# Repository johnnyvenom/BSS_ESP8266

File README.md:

# BSS_ESP8266
ESP8266 scripts and patches for Body:Suit:Score tests

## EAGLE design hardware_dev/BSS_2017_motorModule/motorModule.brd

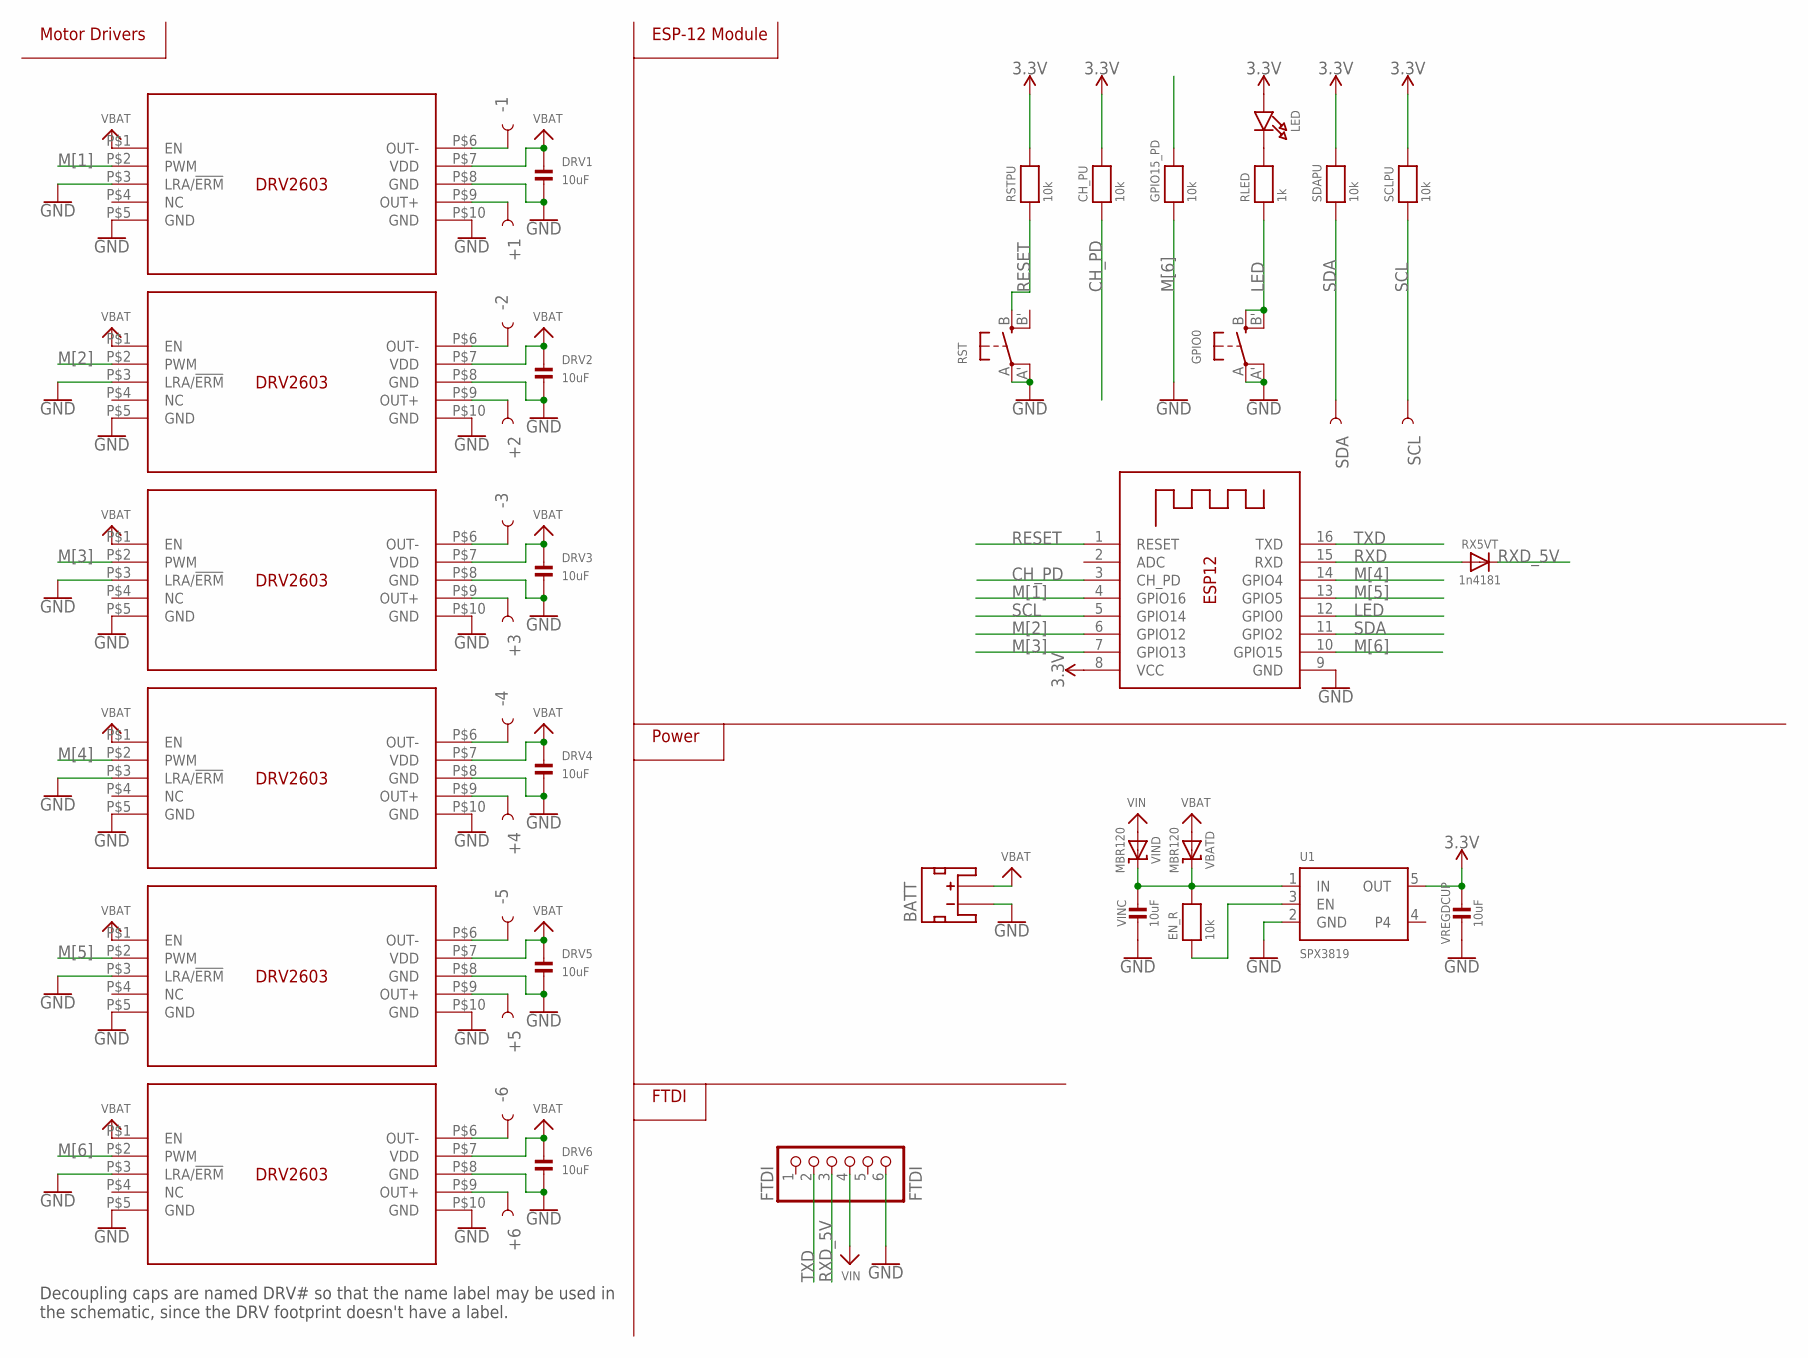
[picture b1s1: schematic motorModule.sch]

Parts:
+1, +2, +3, +4, +5, +6: SEWTAP_SMALL-2SIDE; PETAL-SMALL-2SIDE
-1, -2, -3, -4, -5, -6: SEWTAP_SMALL-2SIDE; PETAL-SMALL-2SIDE
BATT: JST_2MM_MALE; JST-2-SMD
CH_PU: 10k; 0603
DRV1, DRV2, DRV3, DRV4, DRV5, DRV6: 10uF; 0603
DRVIC1, DRVIC2, DRVIC3, DRVIC4, DRVIC5, DRVIC6: DRV2603
EN_R: 10k; 0603
ESP12: ESP-12
FTDI: FTDI; 1X06
GPIO0: SWITCH_TACT_SMT4.6X2.8; BTN_KMR2_4.6X2.8
GPIO15_PD: 10k; 0603
LED: MICROBUILDER_LED0805; MICROBUILDER_CHIPLED_0805
RLED: 1k; 0603
RST: SWITCH_TACT_SMT4.6X2.8; BTN_KMR2_4.6X2.8
RSTPU: 10k; 0603
RX5VT: 1n4181; MICROBUILDER_SOD-323
SCL: SEWTAP_SMALL-2SIDE; PETAL-SMALL-2SIDE
SCLPU: 10k; 0603
SDA: SEWTAP_SMALL-2SIDE; PETAL-SMALL-2SIDE
SDAPU: 10k; 0603
U1: SPX3819; SOT23-5
VBATD: MBR120; MICROBUILDER_SOD-123
VINC: 10uF; MICROBUILDER_0805-NO
VIND: MBR120; MICROBUILDER_SOD-123
VREGDCUP: 10uF; MICROBUILDER_0805-NO

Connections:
3.3V: CH_PU.2, ESP12.8 (VCC), LED.A, RSTPU.2, SCLPU.2, SDAPU.2, U1.5 (OUT), VREGDCUP.1
CH_PD: CH_PU.1, ESP12.3 (CH_PD)
GND: BATT.1 (-), DRV1.2, DRV2.2, DRV3.2, DRV4.2, DRV5.2, DRV6.2, DRVIC1.P$3 (LRA/!ERM), DRVIC1.P$5 (GND), DRVIC1.P$8 (GND), DRVIC1.P$10 (GND), DRVIC2.P$3 (LRA/!ERM), DRVIC2.P$5 (GND), DRVIC2.P$8 (GND), DRVIC2.P$10 (GND), DRVIC3.P$3 (LRA/!ERM), DRVIC3.P$5 (GND), DRVIC3.P$8 (GND), DRVIC3.P$10 (GND), DRVIC4.P$3 (LRA/!ERM), DRVIC4.P$5 (GND), DRVIC4.P$8 (GND), DRVIC4.P$10 (GND), DRVIC5.P$3 (LRA/!ERM), DRVIC5.P$5 (GND), DRVIC5.P$8 (GND), DRVIC5.P$10 (GND), DRVIC6.P$3 (LRA/!ERM), DRVIC6.P$5 (GND), DRVIC6.P$8 (GND), DRVIC6.P$10 (GND), ESP12.9 (GND), FTDI.6, GPIO0.A, GPIO0.A' (P1), GPIO15_PD.1, RST.A, RST.A' (P1), U1.2 (GND), VINC.2, VREGDCUP.2
LDO_EN: EN_R.1, U1.3 (EN)
LED: ESP12.12 (GPIO0), GPIO0.B (S), GPIO0.B' (S1), RLED.1
LEDIN: LED.C, RLED.2
M[1]: DRVIC1.P$2 (PWM), ESP12.4 (GPIO16)
M[2]: DRVIC2.P$2 (PWM), ESP12.6 (GPIO12)
M[3]: DRVIC3.P$2 (PWM), ESP12.7 (GPIO13)
M[4]: DRVIC4.P$2 (PWM), ESP12.14 (GPIO4)
M[5]: DRVIC5.P$2 (PWM), ESP12.13 (GPIO5)
M[6]: DRVIC6.P$2 (PWM), ESP12.10 (GPIO15), GPIO15_PD.2
unnamed: -1.1, DRVIC1.P$6 (OUT-)
unnamed: +1.1, DRVIC1.P$9 (OUT+)
unnamed: -2.1, DRVIC2.P$6 (OUT-)
unnamed: +2.1, DRVIC2.P$9 (OUT+)
unnamed: -3.1, DRVIC3.P$6 (OUT-)
unnamed: +3.1, DRVIC3.P$9 (OUT+)
unnamed: -4.1, DRVIC4.P$6 (OUT-)
unnamed: +4.1, DRVIC4.P$9 (OUT+)
unnamed: -5.1, DRVIC5.P$6 (OUT-)
unnamed: +5.1, DRVIC5.P$9 (OUT+)
unnamed: -6.1, DRVIC6.P$6 (OUT-)
unnamed: +6.1, DRVIC6.P$9 (OUT+)
RESET: ESP12.1 (RESET), RST.B (S), RSTPU.1
RXD: ESP12.15 (RXD), RX5VT.A
RXD_5V: FTDI.3, RX5VT.C
SCL: ESP12.5 (GPIO14), SCL.1, SCLPU.1
SDA: ESP12.11 (GPIO2), SDA.1, SDAPU.1
TXD: ESP12.16 (TXD), FTDI.2
VBAT: BATT.2 (+), DRV1.1, DRV2.1, DRV3.1, DRV4.1, DRV5.1, DRV6.1, DRVIC1.P$1 (EN), DRVIC1.P$7 (VDD), DRVIC2.P$1 (EN), DRVIC2.P$7 (VDD), DRVIC3.P$1 (EN), DRVIC3.P$7 (VDD), DRVIC4.P$1 (EN), DRVIC4.P$7 (VDD), DRVIC5.P$1 (EN), DRVIC5.P$7 (VDD), DRVIC6.P$1 (EN), DRVIC6.P$7 (VDD), VBATD.A
VIN: FTDI.4, VIND.A
VREGIN: EN_R.2, U1.1 (IN), VBATD.C, VINC.1, VIND.C

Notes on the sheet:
Motor Drivers
ESP-12 Module
FTDI
Power
Decoupling caps are named DRV# so that the name label may be used in the schematic, since the DRV footprint doesn't have a label.

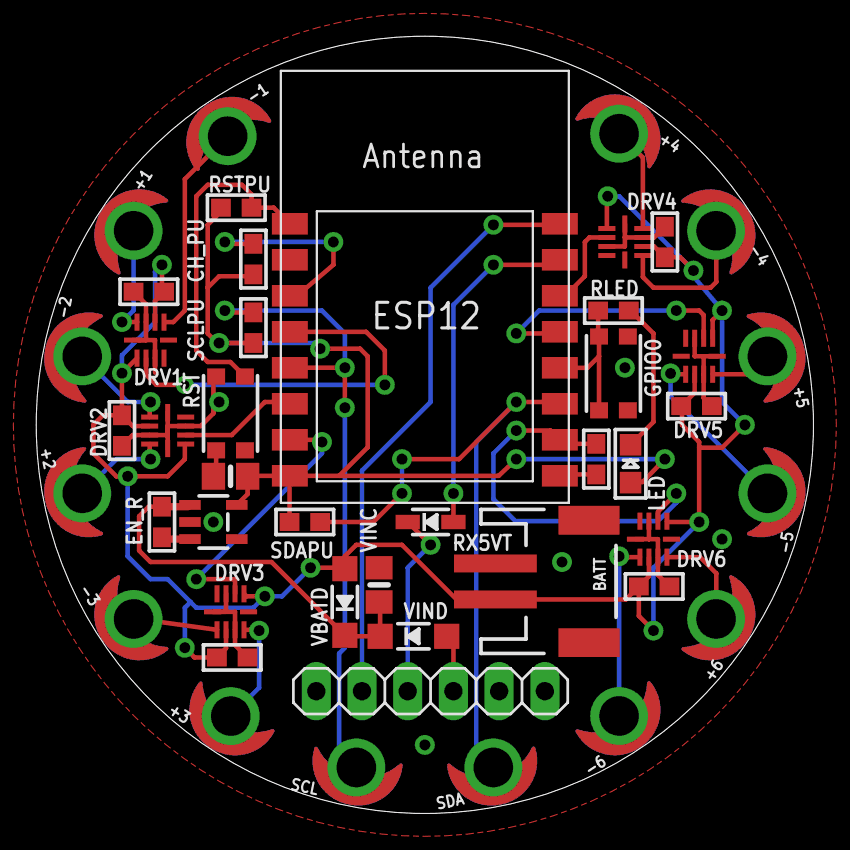
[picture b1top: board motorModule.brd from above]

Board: 2 copper layers, 43.2 x 43.2 mm, 45 parts (0 on the bottom side), 33 nets.

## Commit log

2017-03-03 adds tester scoresheet
2017-03-04 first commit on network discovery
2017-03-04 updates max tester patch
2017-03-04 updates network discovery arduino and max patches
2017-03-04 more work on net discovery
2017-03-04 added net discovery to main patch
2017-03-04 added simulated sensor output method. Send /sensor 1 to enable
2017-03-04 updates BSS_led__test.maxpat
2017-03-05 small change so that ESPs will connect to either secure or unsecure network
2017-03-05 completed tester max patches
2017-03-05 updates subject_scorer.maxpat
2017-03-05 main patch cleanup
2017-03-05 changes sensor data stream timing
2017-03-05 adds raw data files
2017-03-12 experiment data analysis and hardware dev files
2017-03-15 organized and WIP data analysis
2017-03-20 adds analysis

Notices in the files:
parts and their libraries:
microbuilder: This work is placed in the public domain, and may be freely used for commercial and non-commercial work with the following conditions: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
LilyPad-Wearables: Licensing: Creative Commons ShareAlike 4.0 International - https://creativecommons.org/licenses/by-sa/4.0
